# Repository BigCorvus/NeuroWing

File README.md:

# NeuroWing
Feather wing that carries a 2ch bioamplifier board, a HC-05 bluetooth 2 module and some nice little features.

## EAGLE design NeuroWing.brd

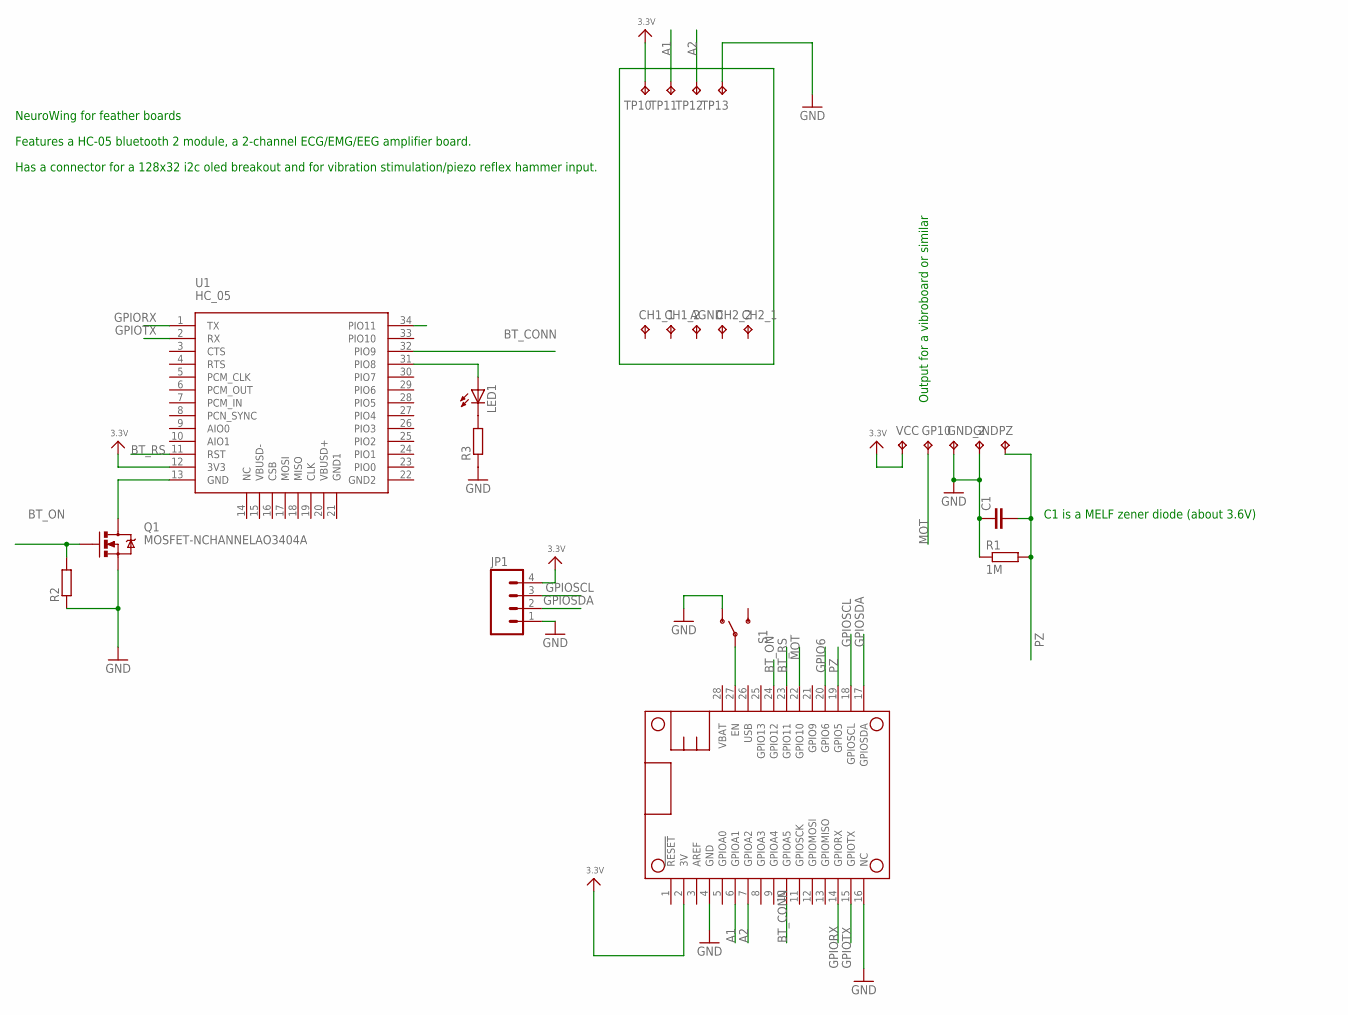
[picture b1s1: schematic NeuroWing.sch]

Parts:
AGND: TPTP17R; TP17R
C1: C-EUC1206; C1206
CH1_1, CH1_2, CH2_1, CH2_2: TPTP17R; TP17R
GND: TPTP20R; TP20R
GND_2: TPTP20R; TP20R
GP10: TPTP20R; TP20R
JP1: M04PTH; 1X04
LED1: LEDCHIP-LED0805; CHIP-LED0805
MS2: FEATHERWING
PZ: TPTP20R; TP20R
Q1: MOSFET-NCHANNELAO3404A; SOT23-3
R1: 1M; R0603
R2, R3: R-EU_R0603; R0603
S1: SWITCH-SPDT-SMD-A; SWITCH-SPST-SMD-A
TP10, TP11, TP12, TP13: TPTP17R; TP17R
U1: HC_05; BLUETOOTH_SMD
VCC: TPTP20R; TP20R

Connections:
3.3V: JP1.4, MS2.2 (3V), TP10.TP, U1.12 (3V3), VCC.TP
A1: MS2.6 (GPIOA1), TP11.TP
A2: MS2.7 (GPIOA2), TP12.TP
BT_CONN: MS2.10 (GPIOA5), U1.32 (PIO9)
BT_ON: MS2.24 (GPIO12), Q1.1 (G), R2.2
BT_RS: MS2.23 (GPIO11), U1.11 (RST)
GND: C1.1, GND.TP, GND_2.TP, JP1.1, MS2.4 (GND), MS2.16 (NC), Q1.2 (S), R1.1, R2.1, R3.1, S1.1 (O), TP13.TP
GPIO6: MS2.20 (GPIO6)
GPIORX: MS2.14 (GPIORX), U1.1 (TX)
GPIOSCL: JP1.3, MS2.18 (GPIOSCL)
GPIOSDA: JP1.2, MS2.17 (GPIOSDA)
GPIOTX: MS2.15 (GPIOTX), U1.2 (RX)
MOT: GP10.TP, MS2.22 (GPIO10)
unnamed: Q1.3 (D), U1.13 (GND)
unnamed: MS2.27 (EN), S1.2
unnamed: LED1.C, R3.2
unnamed: LED1.A, U1.31 (PIO8)
PZ: C1.2, MS2.19 (GPIO5), PZ.TP, R1.2

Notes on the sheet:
NeuroWing for feather boards
Features a HC-05 bluetooth 2 module, a 2-channel ECG/EMG/EEG amplifier board.
Has a connector for a 128x32 i2c oled breakout and for vibration stimulation/piezo reflex hammer input.
C1 is a MELF zener diode (about 3.6V)
Output for a vibroboard or similar

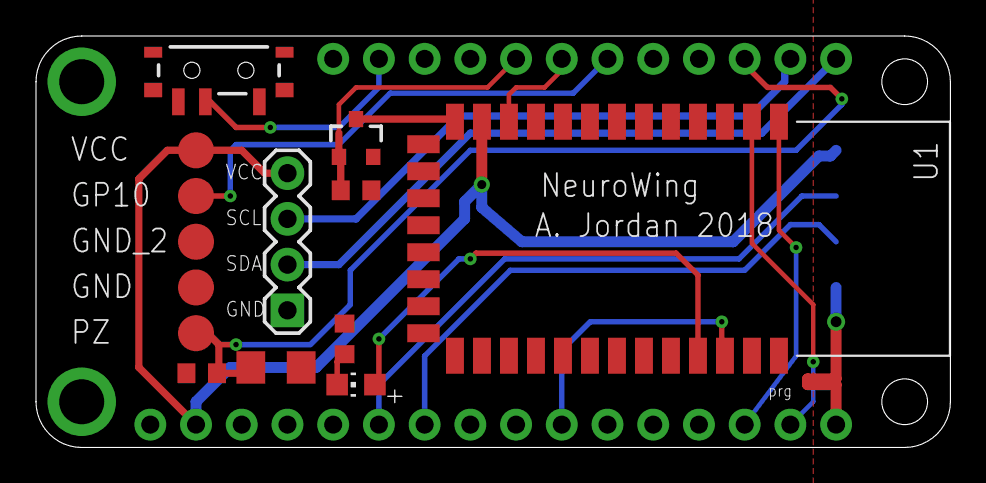
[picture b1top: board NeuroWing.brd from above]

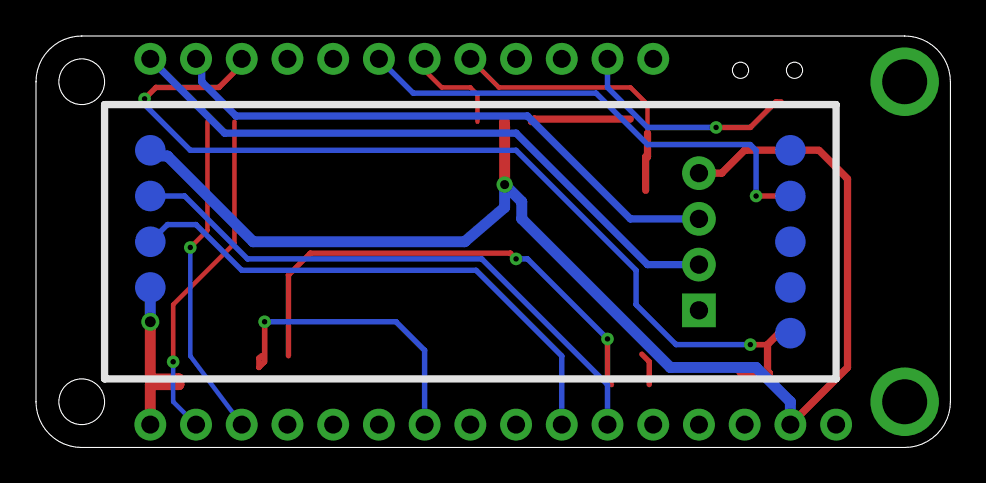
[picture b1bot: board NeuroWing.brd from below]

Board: 2 copper layers, 50.8 x 22.9 mm, 24 parts (9 on the bottom side), 17 nets.

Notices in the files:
parts and their libraries:
microbuilder: This work is placed in the public domain, and may be freely used for commercial and non-commercial work with the following conditions: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
SparkFun-DiscreteSemi: Licensing: Creative Commons ShareAlike 4.0 International - https://creativecommons.org/licenses/by-sa/4.0
